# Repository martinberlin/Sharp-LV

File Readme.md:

### Sharp Low Consumption Versatile PCB

This will host the PCB KiCad files for a  board that aims to be a low consumption driver for SHARP 2.7" MIP LCDs with optional touch.
This is a current work in project and by any means ready to send anywhere to production. The factory we use to produce our prototypes and final PCBs is [JLCPCB.com](https://jlcpcb.com)

### How with touch ?

The person that sold this in eBay had a BTC wallet project that didn't see the light as a product, and combined a Microchip Atmel capacitive touch with a Sharp 400x240 memory LCD:

Resulting in that he has a nice amount of this combination to sell in eBay.

**TOUCH PINOUT**

### Goals to achieve with this board

Just a quick wishlist for this PCB wishes, in version 1.0 just want to get the basics working, no add-ons maybe just a QWIIC connector that is cheap:

1. Display working with external Resonator CrystalFonts RV3032 so the MCU can go to sleep and we can keep the LCD running
2. touch connector with the Molex part  C563931
3. Ready for LVGL
4. BLE working at least for 20 meters receiving and sending data packages

### Reference working designs 

[Altium example for nRF52](https://resources.altium.com/p/getting-started-nrf52-mcu-pcb)

[Mike Rankin Oled PCB](https://github.com/mike-rankin/nRF52832_Oled_Board)

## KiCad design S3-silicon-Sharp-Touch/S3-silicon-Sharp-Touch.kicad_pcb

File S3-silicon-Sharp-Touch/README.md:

# SHARP Light and Versatile controller

The goal of this PCB is to make a small SHARP memory in pixel (MIP) controller
All this might change as the idea develops but initially the plan is the following:

- DS3231 or RV2032 acting as RTC to generate the Squarewave required by this displays
- Optional touch only available in eBay from a seller in the UK (Better use 1.1 version)

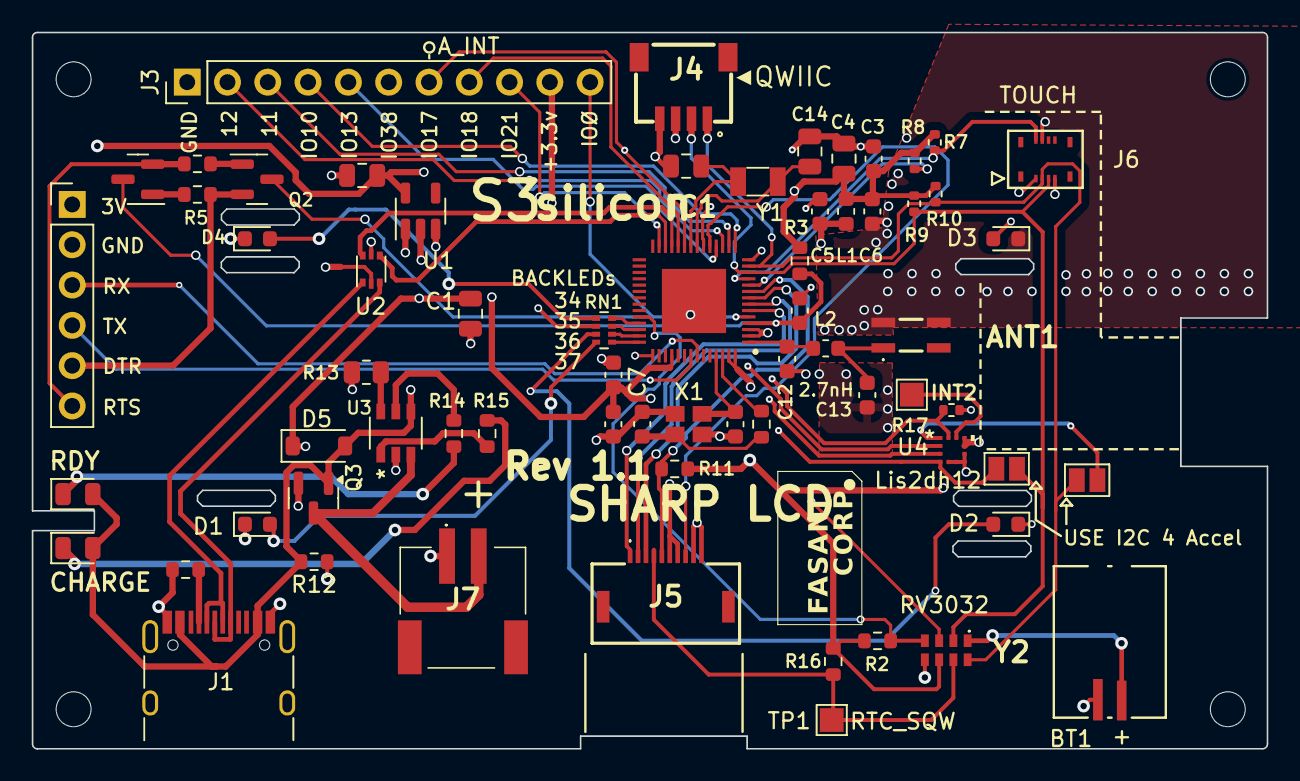
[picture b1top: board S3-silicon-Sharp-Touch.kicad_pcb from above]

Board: 4 copper layers, 77.9 x 45.2 mm, 70 parts (0 on the bottom side), 62 nets.

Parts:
ANT1: 2450AT42E0100E; 2450AT42E0100E-ANT
BT1: Battery_Cell; CoinBattery_MS621FE
C1, C2, C4: 10uF; C_0805_2012Metric
C3, C9: 1uF; C_0603_1608Metric
C5, C6, C7, C8: 0.1uF; C_0603_1608Metric
C10, C11: 22pF; C_0603_1608Metric
C12: 2pF; C_0603_1608Metric
C13: 2.4pF; C_0603_1608Metric
C14, C15: 12pF; C_0805_2012Metric
D1: WHITE LEDs; LED_0603_1608Metric
D2, D3: LED; LED_0603_1608Metric
D4: LED RED; LED_0603_1608Metric
D5: 1N5817; D_SOD-123
D6: GRE; LED_0805_2012Metric
D7: RED; LED_0805_2012Metric
H1, H2, H3, H4: MountingHole; MountingHole_2.2mm_M2
IC1: ESP32-S3FN8; ESP32-S3FN8-QFN40P700X700X90-57N-D
J1: USB_C_Receptacle_USB2.0; USB_C_Receptacle_HRO_TYPE-C-31-M-12
J2: Conn_01x06_Socket; PinHeader_1x06_P2.54mm_Vertical
J3: Conn_01x11_Socket; PinHeader_1x11_P2.54mm_Vertical
J4: SM04B-SRSS-TB_LF__SN_; QWIIC_SM04B-SRSS-TB_LFSN_
J5: FH52-10S-0.5SH_99; FH5210S05SH99_LCD
J6: 5024260810; CON_Molex_5024260812
J7: S2B-PH-SM4-TB_LF__SN_; S2BPHSM4TBLFSN
JP1: Jumper SDA; SolderJumper-2_P1.3mm_Open_Pad1.0x1.5mm
JP2: Jumper SCL; SolderJumper-2_P1.3mm_Open_Pad1.0x1.5mm
L1, L2: L; L_0603_1608Metric
Q1, Q2: MMBT3904; SOT-23
Q3: Si2301CDS; SOT-23
R1, R11, R14, R15: 5.1k; R_0603_1608Metric
R2, R16: 10 K; R_0603_1608Metric
R3, R5, R6: 10k; R_0603_1608Metric
R4: 0Ω; R_0603_1608Metric
R7, R8, R9, R10: 3.3k; R_0402_1005Metric
R12: 10K; R_0603_1608Metric
R13: 2K2; R_0805_2012Metric
R17: 100k; R_0402_1005Metric
RN1: R_Pack04; R_Array_Concave_4x0402
TP1, TP2: RTC_INT; TestPoint_Pad_1.5x1.5mm
U1: RT9080-33GJ5; TSOT-23-5
U2: USBLC6-2P6; SOT-666
U3: TP4057-42-SOT26-R
U4: LIS2DH12TR; LIS2DH12TR_LGA-12_STM_Accel
X1: Crystal 40 Mhz 10ppm; Crystal_ECS-40Mhz_ECS
Y1: 32.768K; Crystal_SMD_3215-2Pin_3.2x1.5mm
Y2: RV-3032-C7; RV3032C7

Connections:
/A_SPI_CS: IC1.16 (GPIO11), J3.3, U4.2 (CS)
/A_SPI_INT1: IC1.23 (GPIO17), J3.7, R17.1, U4.12 (INT1)
/A_SPI_MISO: IC1.18 (GPIO13), J3.5, U4.3 (SDO/SA0)
/A_SPI_MOSI: IC1.15 (GPIO10), J3.4, JP1.2 (B), U4.4 (SDA/SDI/SDO)
/CHIP_PU: C9.2, IC1.4 (CHIP_PU), Q1.3 (C), R3.2
/DTR: J2.5, Q2.2 (E), R5.2
/IO0: IC1.5 (GPIO0), J3.11, Q2.3 (C)
/IO12: IC1.17 (GPIO12), J3.2
/IO18: IC1.24 (GPIO18), J3.8
/IO21: IC1.27 (GPIO21), J3.9
/IO38: IC1.43 (GPIO38), J3.6
/LCD_CS: IC1.8 (GPIO3), J5.3
/LCD_DISPON: IC1.9 (GPIO4), J5.5, R11.2
/LCD_EXTMODE: IC1.19 (GPIO14), J5.8
/RTC_EVI: IC1.38 (GPIO33), R2.2, Y2.4 (EVI)
/RTC_INT: IC1.14 (GPIO9), Y2.3 (~INT)
/RTC_SQW: J5.4, R16.2, TP1.1, Y2.7 (CLKOUT)
/RTS: J2.6, Q1.2 (E), R6.2
/SCL: IC1.13 (GPIO8), J4.1, J6.3, JP2.1 (A), R9.2, Y2.8 (SCL)
/SDA: IC1.12 (GPIO7), J4.2, J6.2, JP1.1 (A), R10.2, Y2.2 (SDA)
/SPI_CLK: IC1.6 (GPIO1), J5.1
/SPI_MOSI: IC1.7 (GPIO2), J5.2
/TOUCH_IRQ: IC1.11 (GPIO6), J6.5, R7.2
/TOUCH_REST: IC1.10 (GPIO5), J6.4, R8.2
/USB_D+: IC1.26 (GPIO20), U2.4 (I/O2)
/USB_D-: IC1.25 (GPIO19), U2.6 (I/O1)
/USB_U_D+: J1.A6 (D+), J1.B6 (D+), U2.3 (I/O2)
/USB_U_D-: J1.A7 (D-), J1.B7 (D-), U2.1 (I/O1)
GND: ANT1.3 (GND_1), ANT1.4 (GND_2), BT1.2 (-), C1.2, C2.1, C3.1, C4.1, C5.1, C6.1, C7.1, C8.1, C9.1, C10.1, C11.1, C12.2, C13.2, C14.1, C15.1, D1.1 (K), D2.1 (K), D3.1 (K), D4.1 (K), IC1.57 (GND), J1.A1 (GND), J1.A12 (GND), J1.B1 (GND), J1.B12 (GND), J1.S1 (SHIELD), J2.2, J3.1, J4.4, J5.9, J5.10, J6.6, J7.1, R1.2, R12.1, R13.1, R17.2, U1.2 (GND), U2.2 (GND), U3.2 (GND), U4.5 (RES), U4.6 (GND), U4.7 (GND), U4.8 (GND), X1.2, X1.4, Y2.5 (VSS)
unnamed: ANT1.1 (FEEDING_POINT), C13.1, L2.1
unnamed: C10.2, R4.2, X1.1
unnamed: D1.2 (A), RN1.4 (R4.1)
unnamed: D2.2 (A), RN1.3 (R3.1)
unnamed: D3.2 (A), RN1.2 (R2.1)
unnamed: D4.2 (A), RN1.1 (R1.1)
unnamed: D6.1 (K), R14.1
unnamed: D7.1 (K), R15.2
unnamed: IC1.39 (GPIO34), RN1.8 (R1.2)
unnamed: IC1.40 (GPIO35), RN1.7 (R2.2)
unnamed: IC1.41 (GPIO36), RN1.6 (R3.2)
unnamed: IC1.42 (GPIO37), RN1.5 (R4.2)
unnamed: C12.1, IC1.1 (LNA_IN), L2.2
unnamed: C5.2, IC1.2 (VDD3P3_1), IC1.3 (VDD3P3_2), L1.2
unnamed: C15.2, IC1.22 (XTAL_32K_N), Y1.2
unnamed: C14.2, IC1.21 (XTAL_32K_P), Y1.1
unnamed: C11.2, IC1.53 (XTAL_N), X1.3
unnamed: IC1.54 (XTAL_P), R4.1
unnamed: J1.A5 (CC1), R1.1
unnamed: JP2.2 (B), U4.1 (SCL/SPC)
unnamed: Q1.1 (B), R5.1
unnamed: Q2.1 (B), R6.1
unnamed: R15.1, U3.1 (*CHRG)
unnamed: R14.2, U3.5 (*STDBY)
unnamed: R13.2, U3.6 (PROG)
unnamed: TP2.1, U4.11 (INT2)
RX: IC1.50 (U0RXD), J2.3
TX: IC1.49 (U0TXD), J2.4
VBAT: J7.2, Q3.3 (D), U3.3 (BAT)
VBUS: D5.2 (A), D6.2 (A), D7.2 (A), J1.A4 (VBUS), J1.A9 (VBUS), J1.B4 (VBUS), J1.B9 (VBUS), Q3.1 (G), R12.2, U2.5 (VBUS), U3.4 (VCC)
VDD: C1.1, D5.1 (K), J5.6, J5.7, Q3.2 (S), U1.1 (VIN), U1.3 (EN)
VDD33: C2.2, C3.2, C4.2, C6.2, C7.2, C8.2, IC1.20 (VDD3P3_RTC), IC1.46 (VDD3P3_CPU), IC1.55 (VDDA_1), IC1.56 (VDDA_2), J2.1, J3.10, J4.3, J6.1, L1.1, R2.1, R3.1, R7.1, R8.1, R9.1, R10.1, R11.1, R16.1, U1.5 (VOUT), U4.9 (VDD), U4.10 (VDD_IO), Y2.6 (VDD)
VDD_RTC: BT1.1 (+), Y2.1 (VBACKUP)

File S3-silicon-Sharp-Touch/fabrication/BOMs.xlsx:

Designator | Footprint | Comment | JLCPCB Part #
J1 | USB_C_Receptacle_HRO_TYPE-C-31-M-12 | USB_C_Receptacle_USB2.0 | C165948
R3,R5,R6 | R_0603_1608Metric | 10k | C25804
X1 | Crystal_ECS-40Mhz_ECS | Crystal 40 Mhz 10ppm | C555614
C4,C1,C2 | C_0805_2012Metric | 10uF | C15850
RN1 | R_Array_Concave_4x0402 | R_Pack04 | C728735
C7,C6,C5,C8 | C_0603_1608Metric | 0.1uF | C3846795
L1,L2 | L_0603_1608Metric | L | C1027
R1,R11,R14,R15 | R_0603_1608Metric | 5.1k | C23186
D6 | LED_0805_2012Metric | GRE | C2297
R7,R8,R9,R10 | R_0402_1005Metric | 3.3k | C5224103
Q2,Q1 | SOT-23 | MMBT3904 | C20526
D2,D1,D4,D3 | LED_0805_2012Metric | LED | C2297
BT1 | CoinBattery_MS621FE | Battery_Cell | C80909
J6 | CON_Molex_5024260812 | 5024260810 | C563931
C3,C9 | C_0603_1608Metric | 1uF | C525331
Q3 | SOT-23 | Si2301CDS | C10487
C15,C14 | C_0805_2012Metric | 12pF | C1792
C10,C11 | C_0603_1608Metric | 22pF | C561172
R4 | R_0603_1608Metric | 0Ω | C21189
C12 | C_0603_1608Metric | 2pF | C162216
R13 | R_0805_2012Metric | 2K2 | C17520
J7 | S2BPHSM4TBLFSN | S2B-PH-SM4-TB_LF__SN_ | C295747
Y1 | Crystal_SMD_3215-2Pin_3.2x1.5mm | 32.768K | C32346
U4 | SOIC-8_3.9x4.9mm_P1.27mm | DS3231MZ | C107410
IC1 | ESP32-S3FN8-QFN40P700X700X90-57N-D | ESP32-S3FN8 | C2913196
D5 | D_SOD-123 | 1N5817 | C8598
U1 | TSOT-23-5 | RT9080-33GJ5 | C841192
R16 | R_0603_1608Metric | 10 K | C25804
C13 | C_0603_1608Metric | 2.4pF | C5448887
D7 | LED_0805_2012Metric | RED | C84256
U3 | TP4057-42-SOT26-R | TP4057-42-SOT26-R | C12044
ANT1 | 2450AT42E0100E-ANT | 2450AT42E0100E | C3285081
R12 | R_0603_1608Metric | 10K | C25804
J5 | FH5210S05SH99_LCD | FH52-10S-0.5SH_99 | C598038
U2 | SOT-666 | USBLC6-2P6 | C2827693

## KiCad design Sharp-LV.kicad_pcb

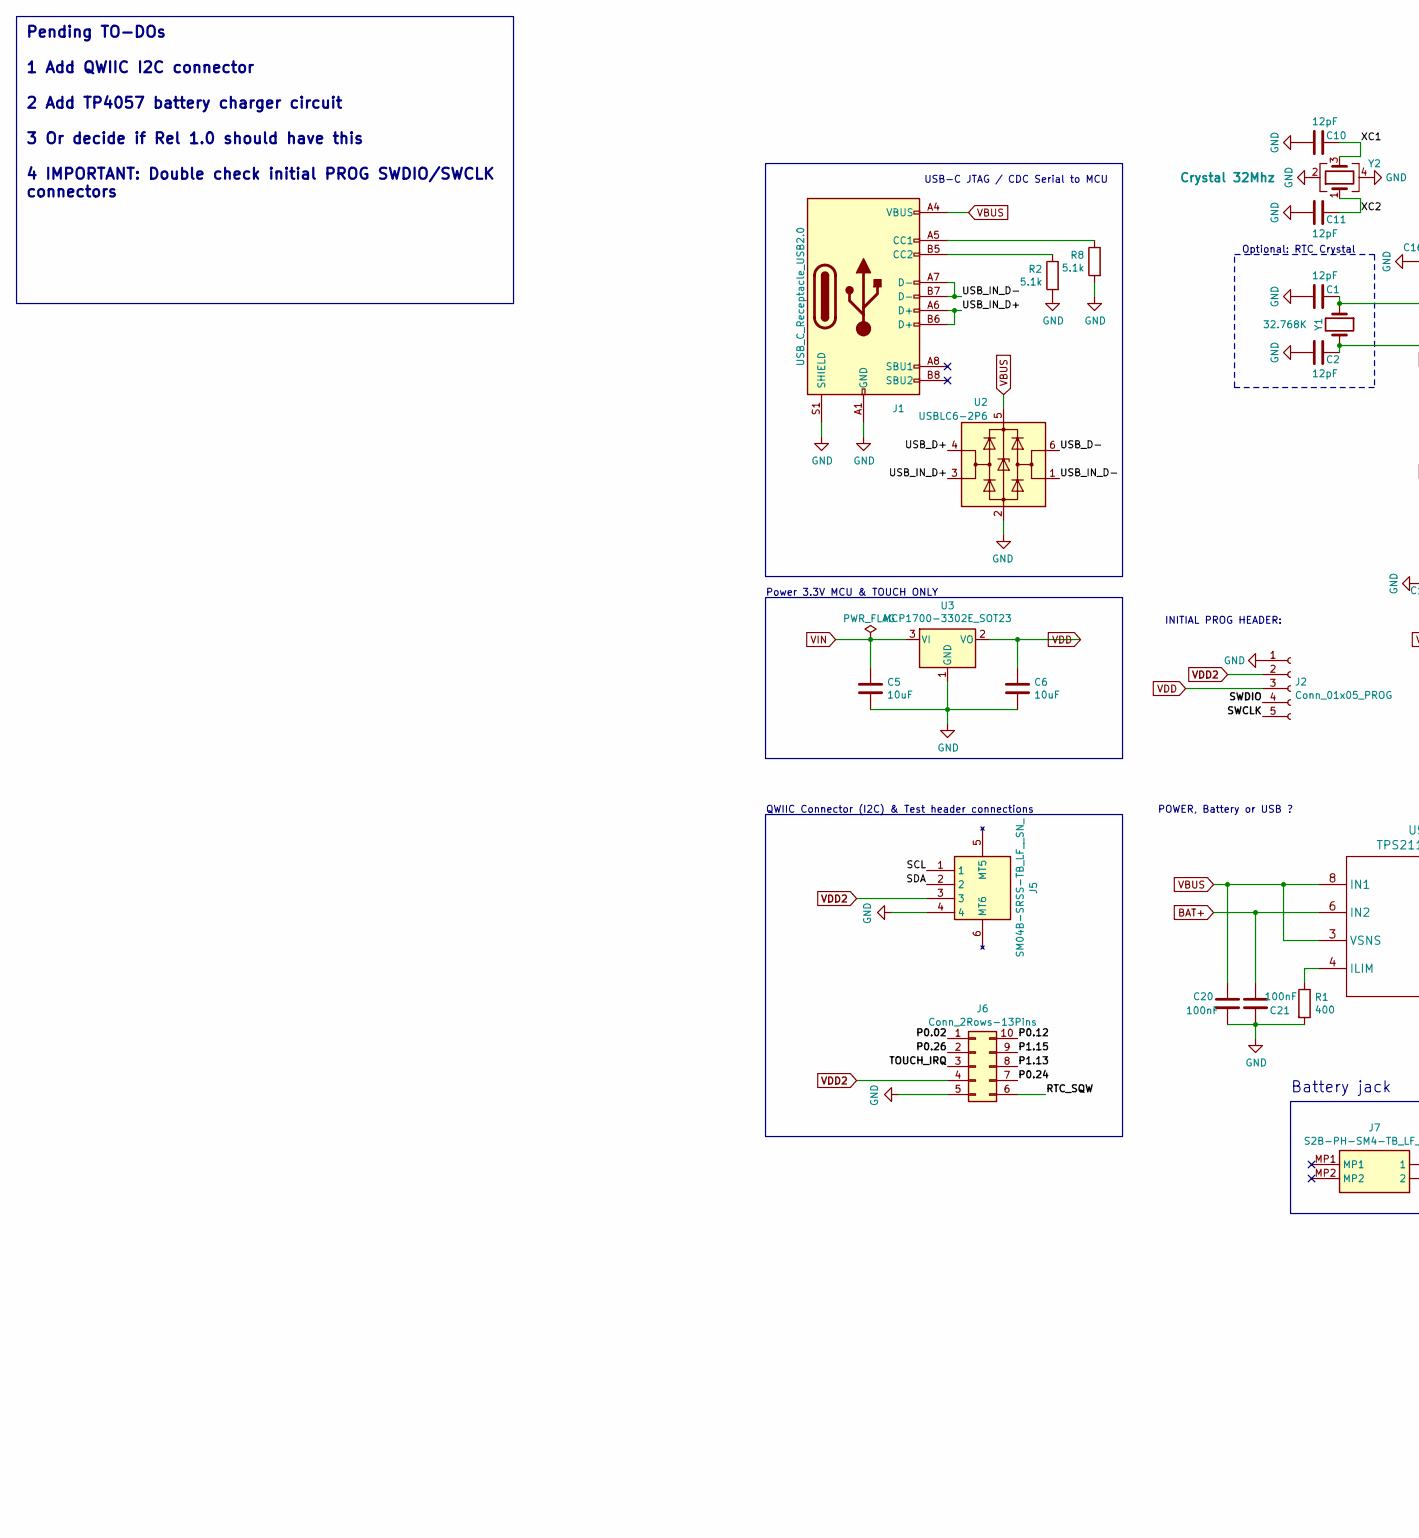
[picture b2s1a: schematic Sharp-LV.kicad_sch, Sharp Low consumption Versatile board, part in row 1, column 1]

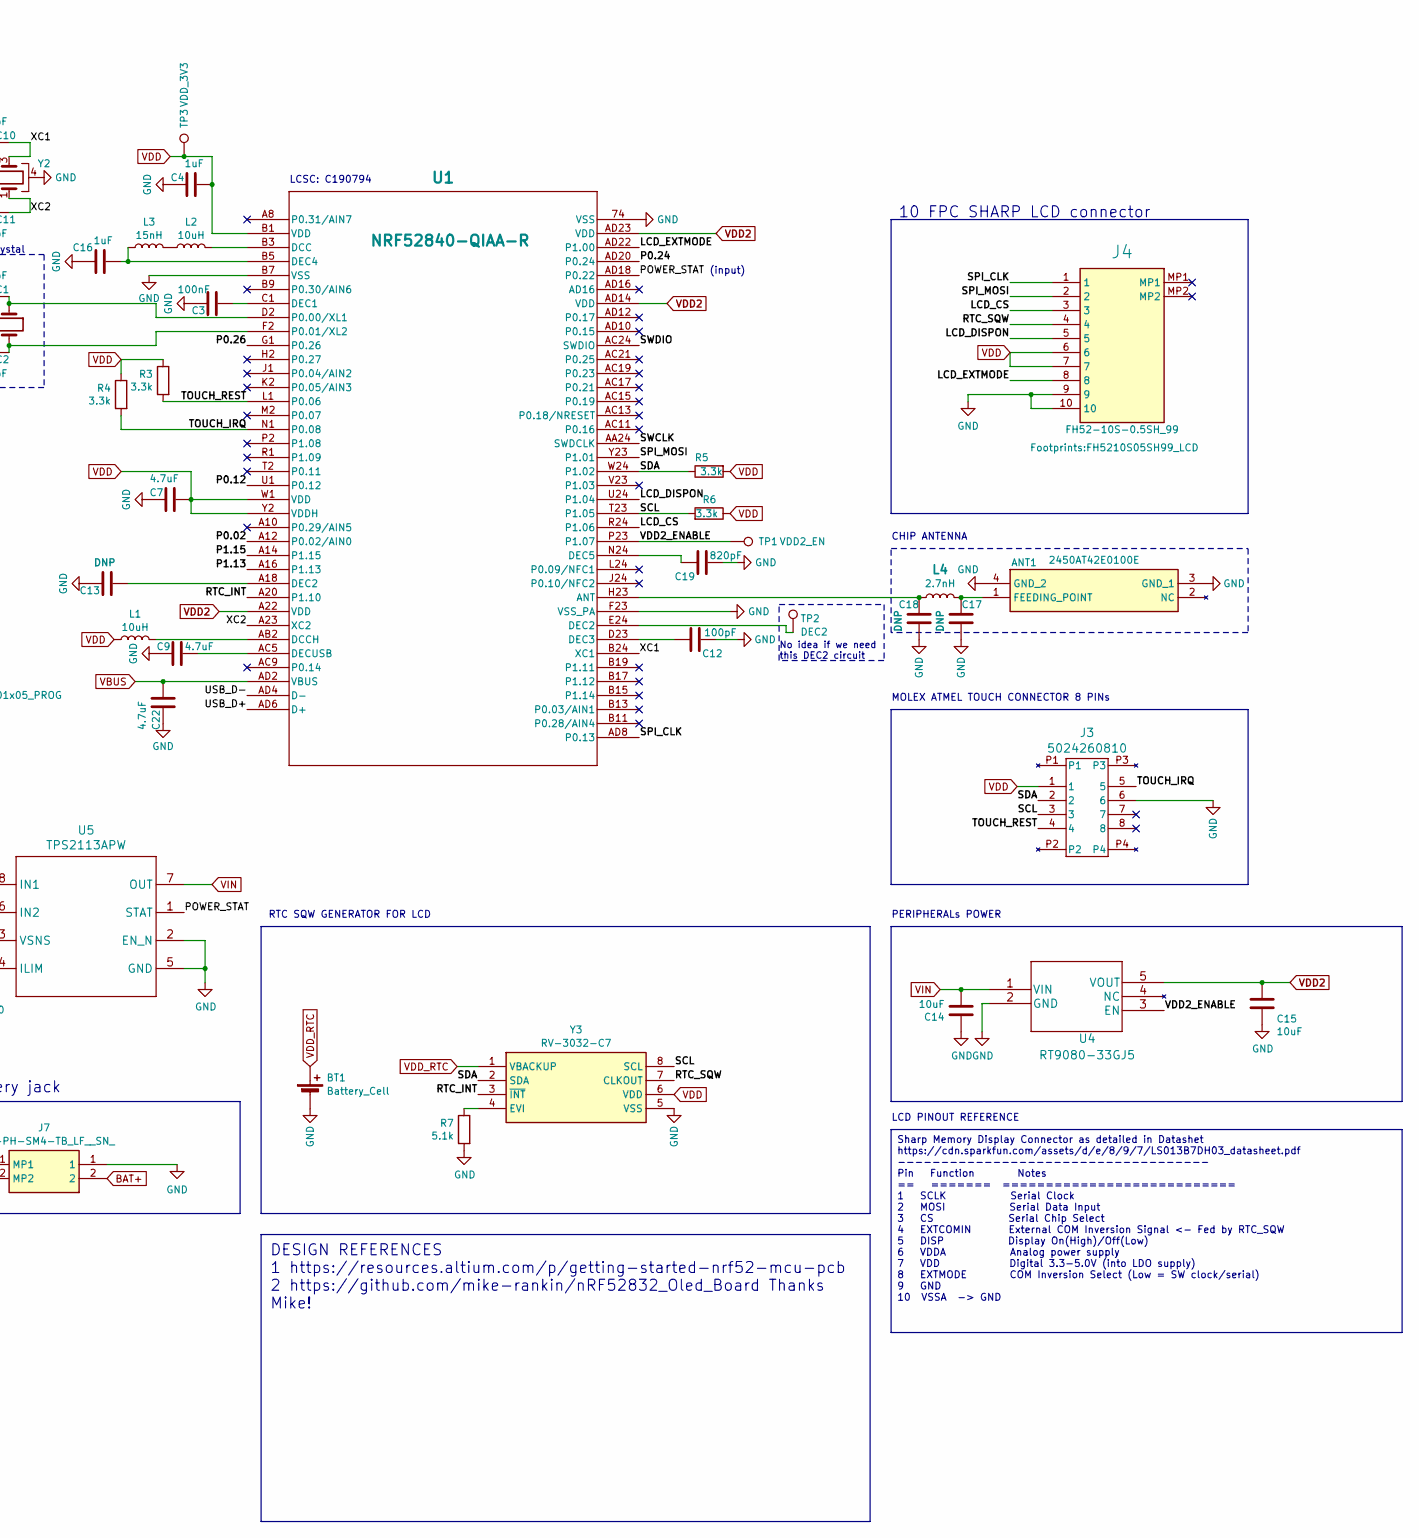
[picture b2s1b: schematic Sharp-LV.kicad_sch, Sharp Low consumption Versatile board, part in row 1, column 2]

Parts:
ANT1: 2450AT42E0100E; 2450AT42E0100E-ANT; LCSC C3285081
BT1: Battery_Cell; CoinBattery_MS621FE; LCSC C80909
C1, C2, C10, C11: 12pF; C_0402_1005Metric; LCSC C386126
C3: 100nF; C_0402_1005Metric; LCSC C5137468
C4, C16: 1uF; C_0201_0603Metric; LCSC C97888
C5, C6, C14, C15: 10uF; C_0805_2012Metric; LCSC C15850
C7, C9, C22: 4.7uF; C_0402_1005Metric; LCSC C23733
C12: 100pF; C_0201_0603Metric; LCSC C531423
C13, C17, C18: DNP; C_0402_1005Metric; LCSC Leave empty
C19: 820pF; C_0402_1005Metric; LCSC C2891595
C20, C21: 100nF; C_0805_2012Metric; LCSC C49678
J1: USB_C_Receptacle_USB2.0; USB_C_Receptacle_HRO_TYPE-C-31-M-12; LCSC C165948
J2: Conn_01x05_PROG; PinHeader_1x05_P2.54mm_Vertical
J3: 5024260810; CON_Molex_5024260812; LCSC C563931
J4: FH52-10S-0.5SH_99; FH5210S05SH99_LCD; Manufacturer_Part_Number FH52-10S-0.5SH(99); JLCPCB Part # C598038
J5: SM04B-SRSS-TB_LF__SN_; QWIIC_SM04B-SRSS-TB_LFSN_; Manufacturer_Part_Number SM04B-SRSS-TB(LF)(SN); LCSC C160404
J6: Conn_2Rows-13Pins; Samtec_HLE-105-02-xxx-DV-A_2x05_P2.54mm_Horizontal
J7: S2B-PH-SM4-TB_LF__SN_; S2BPHSM4TBLFSN; Manufacturer_Part_Number S2B-PH-SM4-TB(LF)(SN); LCSC C295747
L1, L2: 10uH; L_0603_1608Metric; LCSC C373750
L3: 15nH; L_0603_1608Metric; LCSC C2757919
L4: 2.7nH; L_0603_1608Metric; LCSC C5252358
R1: 400; R_0603_1608Metric; LCSC C23151
R2, R7, R8: 5.1k; R_0603_1608Metric; LCSC C23186
R3, R4, R5, R6: 3.3k; R_0402_1005Metric; LCSC C5224103
TP1: VDD2_EN; TestPoint_Pad_D1.5mm
TP2: DEC2; TestPoint_Pad_D1.0mm
TP3: VDD_3V3; TestPoint_Pad_D1.5mm
U1: NRF52840-QIAA-R; NRF52840_AQFN73_7X7_NOR; LCSC C190794
U2: USBLC6-2P6; SOT-666; LCSC C2827693
U3: MCP1700-3302E_SOT23; SOT-23; LCSC C39051
U4: RT9080-33GJ5; TSOT-23-5; LCSC C841192
U5: TPS2113APW; TPS2113APWR; LCSC C130052
Y1: 32.768K; Crystal_SMD_3215-2Pin_3.2x1.5mm; LCSC C32346
Y2: Crystal 32Mhz; Crystal_SMD_2016-4Pin_2.0x1.6mm; LCSC C409316
Y3: RV-3032-C7; RV3032C7; Manufacturer_Part_Number RV-3032-C7; LCSC C5127802

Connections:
/LCD_CS: J4.3, U1.R24 (P1.06)
/LCD_DISPON: J4.5, U1.U24 (P1.04)
/LCD_EXTMODE: J4.8, U1.AD22 (P1.00)
/P0.02: J6.1, U1.A12 (P0.02/AIN0)
/P0.12: J6.10, U1.U1 (P0.12)
/P0.24: J6.7, U1.AD20 (P0.24)
/P0.26: J6.2, U1.G1 (P0.26)
/P1.13: J6.8, U1.A16 (P1.13)
/P1.15: J6.9, U1.A14 (P1.15)
/POWER_STAT: U1.AD18 (P0.22), U5.1 (STAT)
/RTC_INT: U1.A20 (P1.10), Y3.3 (~INT)
/RTC_SQW: J4.4, J6.6, Y3.7 (CLKOUT)
/SCL: J3.3, J5.1, R6.2, U1.T23 (P1.05), Y3.8 (SCL)
/SDA: J3.2, J5.2, R5.1, U1.W24 (P1.02), Y3.2 (SDA)
/SPI_CLK: J4.1, U1.AD8 (P0.13)
/SPI_MOSI: J4.2, U1.Y23 (P1.01)
/SWCLK: J2.5, U1.AA24 (SWDCLK)
/SWDIO: J2.4, U1.AC24 (SWDIO)
/TOUCH_IRQ: J3.5, J6.3, R4.2, U1.N1 (P0.08)
/TOUCH_REST: J3.4, R3.2, U1.L1 (P0.06)
/USB_D+: U1.AD6 (D+), U2.4 (I/O2)
/USB_D-: U1.AD4 (D-), U2.6 (I/O1)
/USB_IN_D+: J1.A6 (D+), J1.B6 (D+), U2.3 (I/O2)
/USB_IN_D-: J1.A7 (D-), J1.B7 (D-), U2.1 (I/O1)
/VDD2_ENABLE: TP1.1, U1.P23 (P1.07), U4.3 (EN)
/XC1: C10.2, U1.B24 (XC1), Y2.3
/XC2: C11.2, U1.A23 (XC2), Y2.1
BAT+: C21.2, J7.2, U5.6 (IN2)
GND: ANT1.3 (GND_1), ANT1.4 (GND_2), BT1.2 (-), C1.1, C2.1, C3.1, C4.1, C5.1, C6.1, C7.1, C9.1, C10.1, C11.1, C12.1, C13.1, C14.2, C15.1, C16.1, C17.1, C18.1, C19.2, C20.2, C21.1, C22.1, J1.A1 (GND), J1.A12 (GND), J1.B1 (GND), J1.B12 (GND), J1.S1 (SHIELD), J2.1, J3.6, J4.9, J4.10, J5.4, J6.5, J7.1, R1.2, R2.2, R7.2, R8.2, U1.74 (VSS), U1.B7 (VSS), U1.F23 (VSS_PA), U2.2 (GND), U3.1 (GND), U4.2 (GND), U5.2 (EN_N), U5.5 (GND), Y2.2, Y2.4, Y3.5 (VSS)
unnamed: ANT1.1 (FEEDING_POINT), C17.2, L4.2
unnamed: C13.2, U1.A18 (DEC2)
unnamed: J1.A5 (CC1), R8.1
unnamed: J1.B5 (CC2), R2.1
unnamed: L2.1, L3.2
unnamed: TP2.1, U1.E24 (DEC2)
unnamed: C18.2, L4.1, U1.H23 (ANT)
unnamed: L2.2, U1.B3 (DCC)
unnamed: L1.2, U1.AB2 (DCCH)
unnamed: C3.2, U1.C1 (DEC1)
unnamed: C12.2, U1.D23 (DEC3)
unnamed: C16.2, L3.1, U1.B5 (DEC4)
unnamed: C19.1, U1.N24 (DEC5)
unnamed: C9.2, U1.AC5 (DECUSB)
unnamed: C1.2, U1.D2 (P0.00/XL1), Y1.1
unnamed: C2.2, U1.F2 (P0.01/XL2), Y1.2
unnamed: R1.1, U5.4 (ILIM)
unnamed: R7.1, Y3.4 (EVI)
VBUS: C20.1, C22.2, J1.A4 (VBUS), J1.A9 (VBUS), J1.B4 (VBUS), J1.B9 (VBUS), U1.AD2 (VBUS), U2.5 (VBUS), U5.3 (VSNS), U5.8 (IN1)
VDD: C4.2, C6.2, C7.2, J2.3, J3.1, J4.6, J4.7, L1.1, R3.1, R4.1, R5.2, R6.1, TP3.1, U1.B1 (VDD), U1.W1 (VDD), U1.Y2 (VDDH), U3.2 (VO), Y3.6 (VDD)
VDD2: C15.2, J2.2, J5.3, J6.4, U1.A22 (VDD), U1.AD14 (VDD), U1.AD23 (VDD), U4.5 (VOUT)
VDD_RTC: BT1.1 (+), Y3.1 (VBACKUP)
VIN: C5.2, C14.1, U3.3 (VI), U4.1 (VIN), U5.7 (OUT)

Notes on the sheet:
DESIGN REFERENCES 1 https://resources.altium.com/p/getting-started-nrf52-mcu-pcb 2 https://github.com/mike-rankin/nRF52832_Oled_Board Thanks Mike!
Sharp Memory Display Connector as detailed in Datashet https://cdn.sparkfun.com/assets/d/e/8/9/7/LS013B7DH03_datasheet.pdf ------------------------------------ Pin Function Notes == ======= =========================== 1 SCLK Serial Clock 2 MOSI Serial Data Input 3 CS Serial Chip Select 4 EXTCOMIN E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
Pending TO-DOs 1 Add QWIIC I2C connector 2 Add TP4057 battery charger circuit 3 Or decide if Rel 1.0 should have this 4 IMPORTANT: Double check initial PROG SWDIO/SWCLK connectors
USB-C JTAG / CDC Serial to MCU
Power 3.3V MCU & TOUCH ONLY
No idea if we need this DEC2 circuit
10 FPC SHARP LCD connector
Battery jack
PERIPHERALs POWER
INITIAL PROG HEADER:
CHIP ANTENNA
LCD PINOUT REFERENCE
(input)
LCSC: C190794
MOLEX ATMEL TOUCH CONNECTOR 8 PINs
RTC SQW GENERATOR FOR LCD
Optional: RTC Crystal
QWIIC Connector (I2C) & Test header connections
POWER, Battery or USB ?

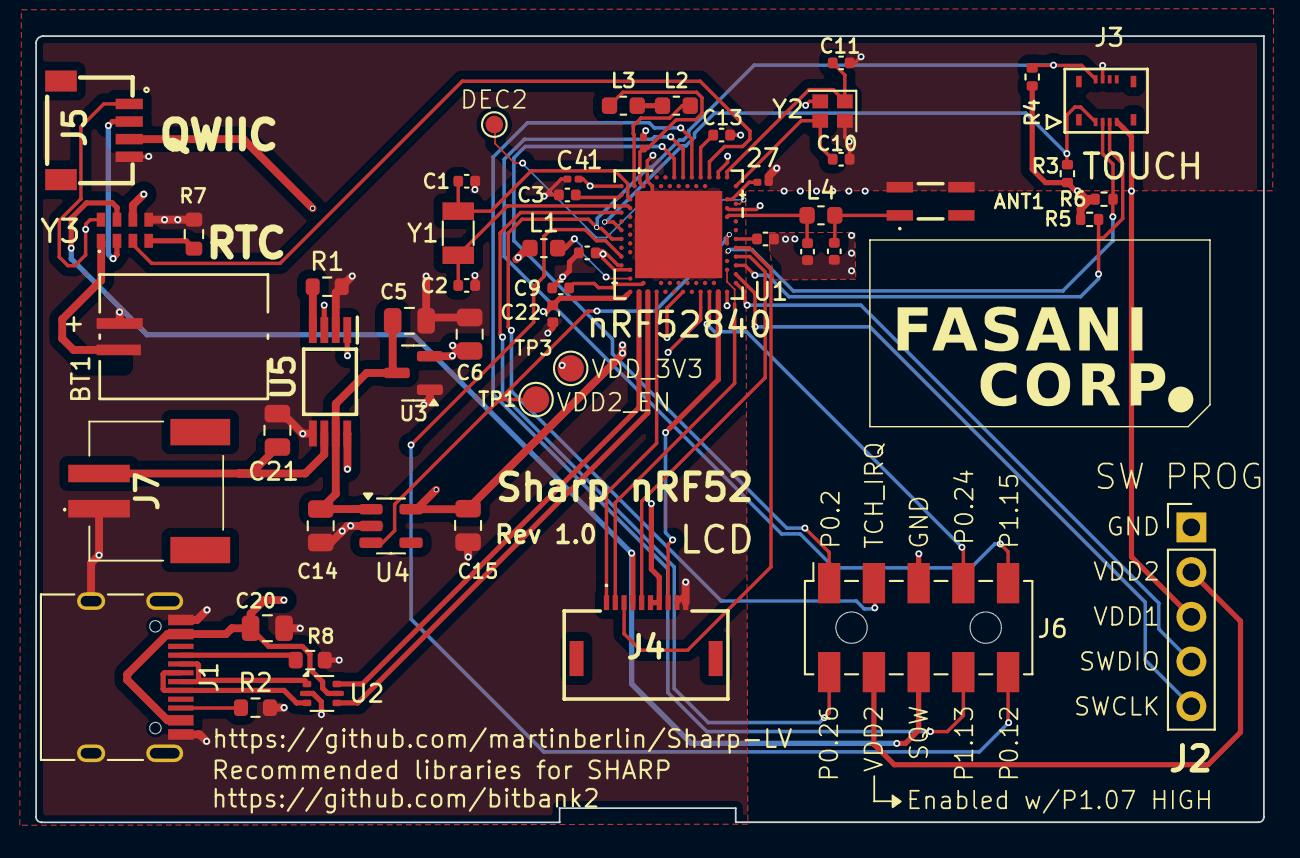
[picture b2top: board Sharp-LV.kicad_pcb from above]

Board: 4 copper layers, 69.7 x 44.7 mm, 53 parts (0 on the bottom side), 52 nets.

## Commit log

2024-05-29 Initial push
2024-05-29 1.0 starting to take shape: Add LCD & touch CONN
2024-05-29 Release 1.0 pending review
2024-05-30 Revision 1.0 silk
2024-06-07 Firmware probes
2024-06-07 Working I2C scanner in Zephyr
2024-06-07 Suitable Readme
2024-06-07 Switch to md
2024-06-08 Touch mxt_init
2024-06-11 Add QWIIC & headers
2024-06-12 Add power mux TPS2113
2024-06-13 Update battery connector & add SCH pdf
2024-06-14 Update crystal to the one provided by Mike (32 Mhz)
2024-06-14 update schematic
2024-06-16 Update SCH and add C22 to VUSB
2024-06-16 Update SCH & DRC
2024-06-18 Update schematics
2024-06-18 Add GND pane
2024-06-19 Add Arduino sketch for bb_Captouch
2024-06-19 Add readme to Firmware
2024-06-20 Update S3 routing proposal
2024-06-20 Update S3 silk
2024-06-25 1.0 sent to fabrication
2024-06-26 Update BT1 routing because bad polarity
2024-06-27 Move touch 2 mm right
2024-07-06 Corrections heading to Rev 1.1 (Bottom ROW of Touch RIGHT!)
2024-07-06 Update TOUCH pinout in PCBs
2024-07-07 Heading for Rel 1.1
2024-07-08 Add Ardino example with @bitbank2 libraries
2024-07-10 S3 release 1.1 is ready
2024-07-17 S3 PCB 3D stl file
2024-07-18 Add 3D printable enclosure
2024-07-18 Update top enclosure
2024-07-18 Create FUNDING.yml
    If you like this PCB then we will appreciate you get one from our store
2024-07-19 Update TOP enclosure with touch cavity
2024-07-19 Update RTC with RV-3032
2024-07-22 1.1 cut-outs
2024-07-24 Use only Via > 0.2 (hole) / 0.45 (pad)
2024-07-25 Add U4:Accelerometer
2024-07-25 Update SCH
2024-07-26 Add pullup to int1 (Accel)
2024-07-26 Update INT1 to be pull-down

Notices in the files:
parts and their libraries:
Copyright 2021 Accelerated Designs. All rights reserved.
